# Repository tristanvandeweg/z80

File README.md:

# z80

Our awesome z80 computer!
<br />
# This project is still a work in progress

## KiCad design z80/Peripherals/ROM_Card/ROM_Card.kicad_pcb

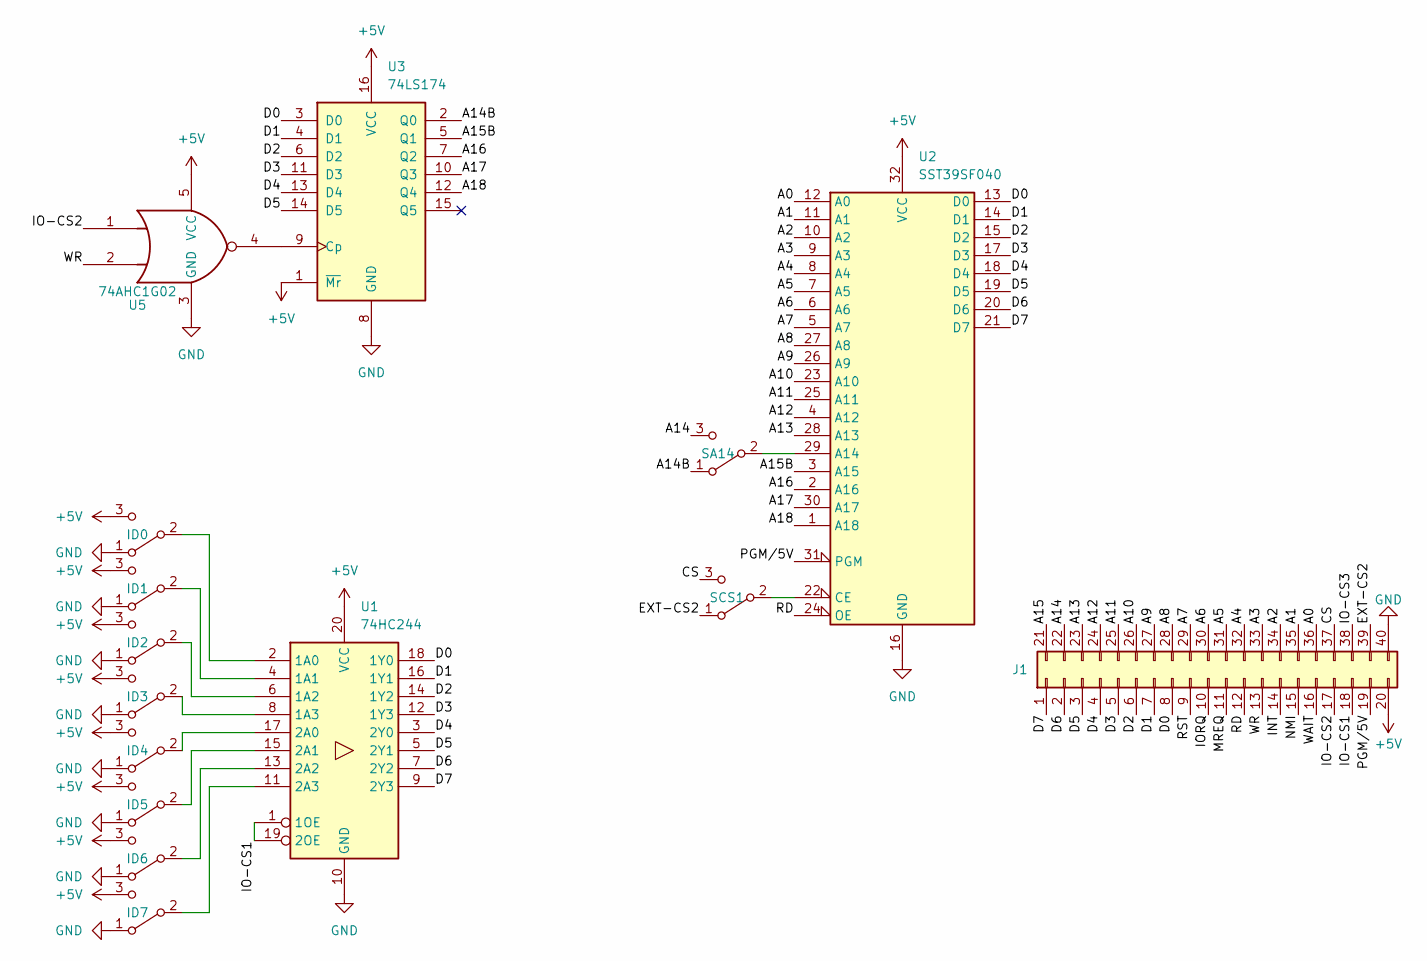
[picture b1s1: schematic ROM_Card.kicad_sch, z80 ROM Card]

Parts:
ID0, ID1, ID2, ID3, ID4, ID5, ID6, ID7: SW_SPDT; SolderJumper-3_P1.3mm_Open_Pad1.0x1.5mm
J1: Conn_02x20_Top_Bottom; 40-pin-edgeconnector
SA14: SW_SPDT; SolderJumper-3_P1.3mm_Open_Pad1.0x1.5mm
SCS1: SW_SPDT; SolderJumper-3_P1.3mm_Open_Pad1.0x1.5mm
U1: 74HC244; TSSOP-20_4.4x6.5mm_P0.65mm
U2: SST39SF040; PLCC-32_THT-Socket
U3: 74LS174; TSSOP-16_4.4x5mm_P0.65mm
U5: 74AHC1G02; SOT-553

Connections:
+5V: ID0.3 (C), ID1.3 (C), ID2.3 (C), ID3.3 (C), ID4.3 (C), ID5.3 (C), ID6.3 (C), ID7.3 (C), J1.20, U1.20 (VCC), U2.32 (VCC), U3.1 (~Mr), U3.16 (VCC), U5.5 (VCC)
/A0: J1.36, U2.12 (A0)
/A1: J1.35, U2.11 (A1)
/A2: J1.34, U2.10 (A2)
/A3: J1.33, U2.9 (A3)
/A4: J1.32, U2.8 (A4)
/A5: J1.31, U2.7 (A5)
/A6: J1.30, U2.6 (A6)
/A7: J1.29, U2.5 (A7)
/A8: J1.28, U2.27 (A8)
/A9: J1.27, U2.26 (A9)
/A10: J1.26, U2.23 (A10)
/A11: J1.25, U2.25 (A11)
/A12: J1.24, U2.4 (A12)
/A13: J1.23, U2.28 (A13)
/A14: J1.22, SA14.3 (C)
/A14B: SA14.1 (A), U3.2 (Q0)
/A15: J1.21
/A15B: U2.3 (A15), U3.5 (Q1)
/A16: U2.2 (A16), U3.7 (Q2)
/A17: U2.30 (A17), U3.10 (Q3)
/A18: U2.1 (A18), U3.12 (Q4)
/CS: J1.37, SCS1.3 (C)
/D0: J1.8, U1.18 (1Y0), U2.13 (D0), U3.3 (D0)
/D1: J1.7, U1.16 (1Y1), U2.14 (D1), U3.4 (D1)
/D2: J1.6, U1.14 (1Y2), U2.15 (D2), U3.6 (D2)
/D3: J1.5, U1.12 (1Y3), U2.17 (D3), U3.11 (D3)
/D4: J1.4, U1.3 (2Y0), U2.18 (D4), U3.13 (D4)
/D5: J1.3, U1.5 (2Y1), U2.19 (D5), U3.14 (D5)
/D6: J1.2, U1.7 (2Y2), U2.20 (D6)
/D7: J1.1, U1.9 (2Y3), U2.21 (D7)
/EXT-CS2: J1.39, SCS1.1 (A)
/INT: J1.14
/IO-CS1: J1.18, U1.1 (1OE), U1.19 (2OE)
/IO-CS2: J1.17, U5.1
/IO-CS3: J1.38
/IORQ: J1.10
/MREQ: J1.11
/NMI: J1.15
/PGM/5V: J1.19, U2.31 (PGM)
/RD: J1.12, U2.24 (OE)
/RST: J1.9
/WAIT: J1.16
/WR: J1.13, U5.2
GND: ID0.1 (A), ID1.1 (A), ID2.1 (A), ID3.1 (A), ID4.1 (A), ID5.1 (A), ID6.1 (A), ID7.1 (A), J1.40, U1.10 (GND), U2.16 (GND), U3.8 (GND), U5.3 (GND)
unnamed: ID0.2 (B), U1.2 (1A0)
unnamed: ID1.2 (B), U1.4 (1A1)
unnamed: ID2.2 (B), U1.6 (1A2)
unnamed: ID3.2 (B), U1.8 (1A3)
unnamed: ID4.2 (B), U1.17 (2A0)
unnamed: ID5.2 (B), U1.15 (2A1)
unnamed: ID6.2 (B), U1.13 (2A2)
unnamed: ID7.2 (B), U1.11 (2A3)
unnamed: SA14.2 (B), U2.29 (A14)
unnamed: SCS1.2 (B), U2.22 (CE)
unnamed: U3.9 (Cp), U5.4

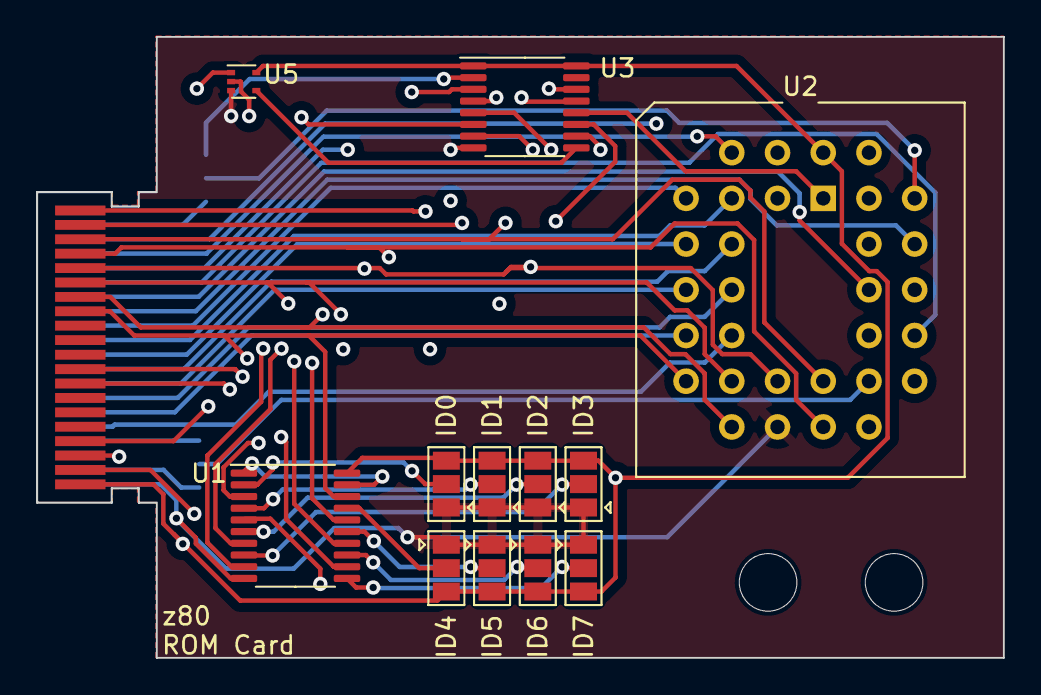
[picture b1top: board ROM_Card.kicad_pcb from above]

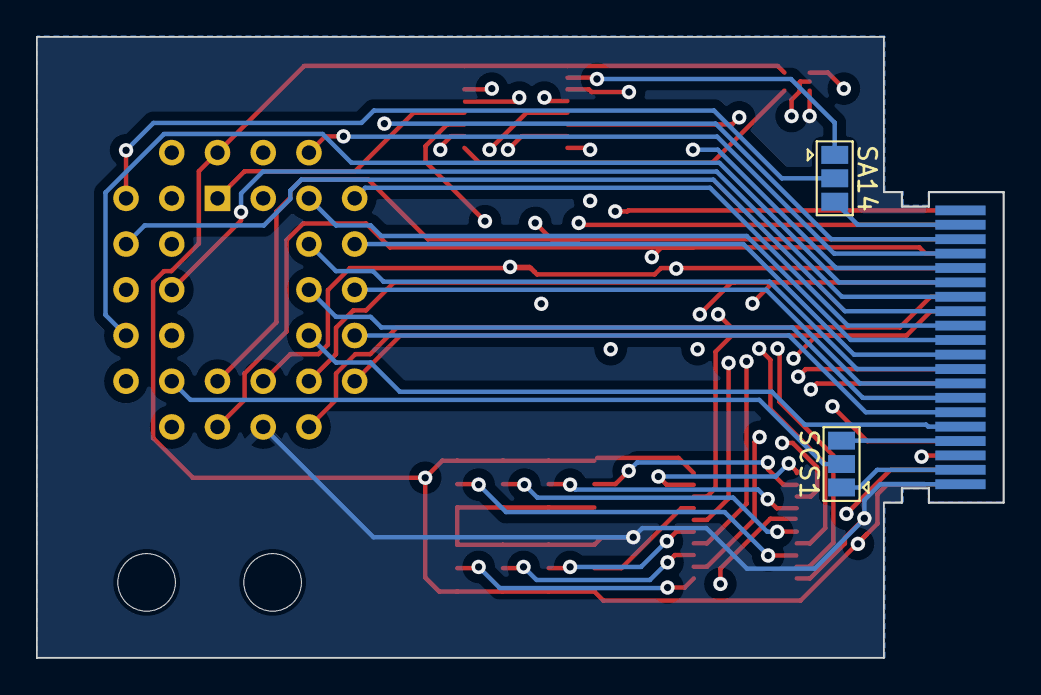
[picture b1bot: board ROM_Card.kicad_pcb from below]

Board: 4 copper layers, 53.7 x 34.5 mm, 15 parts (2 on the bottom side), 48 nets.

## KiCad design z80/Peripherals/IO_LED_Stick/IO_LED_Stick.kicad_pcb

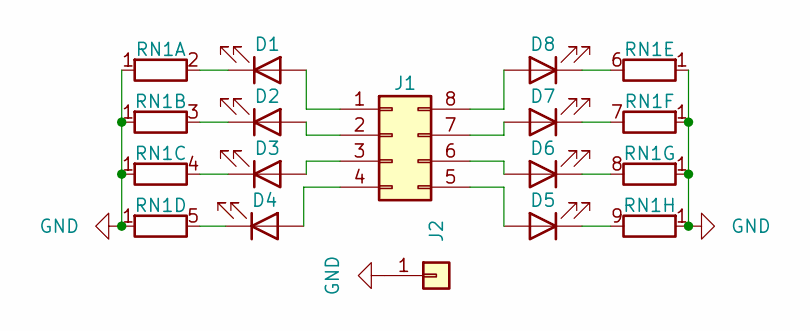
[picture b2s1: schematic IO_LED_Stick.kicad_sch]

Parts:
D1, D2, D3, D4, D5, D6, D7, D8: LED; LED_0603_1608Metric
J1: Conn_02x04_Counter_Clockwise; PinHeader_2x04_P2.54mm_Vertical
J2: Conn_01x01; PinHeader_1x01_P2.54mm_Vertical
RN1: R_Network08_Split; EXB-D10C103J

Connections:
GND: J2.1, RN1.1 (R1)
unnamed: D1.2 (A), J1.1
unnamed: D1.1 (K), RN1.2 (R1.2)
unnamed: D2.2 (A), J1.2
unnamed: D2.1 (K), RN1.3 (R2.2)
unnamed: D3.2 (A), J1.3
unnamed: D3.1 (K), RN1.4 (R3.2)
unnamed: D4.2 (A), J1.4
unnamed: D4.1 (K), RN1.5 (R4.2)
unnamed: D5.2 (A), J1.5
unnamed: D5.1 (K), RN1.9 (R8.2)
unnamed: D6.2 (A), J1.6
unnamed: D6.1 (K), RN1.8 (R7.2)
unnamed: D7.2 (A), J1.7
unnamed: D7.1 (K), RN1.7 (R6.2)
unnamed: D8.2 (A), J1.8
unnamed: D8.1 (K), RN1.6 (R5.2)

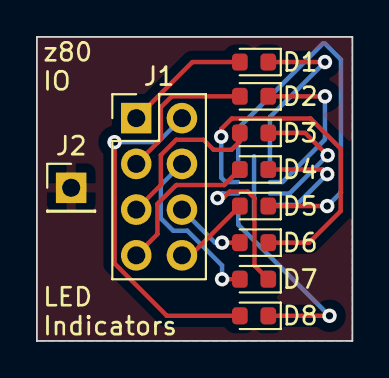
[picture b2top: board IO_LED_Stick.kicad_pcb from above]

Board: 2 copper layers, 17.5 x 16.9 mm, 11 parts (1 on the bottom side), 17 nets.

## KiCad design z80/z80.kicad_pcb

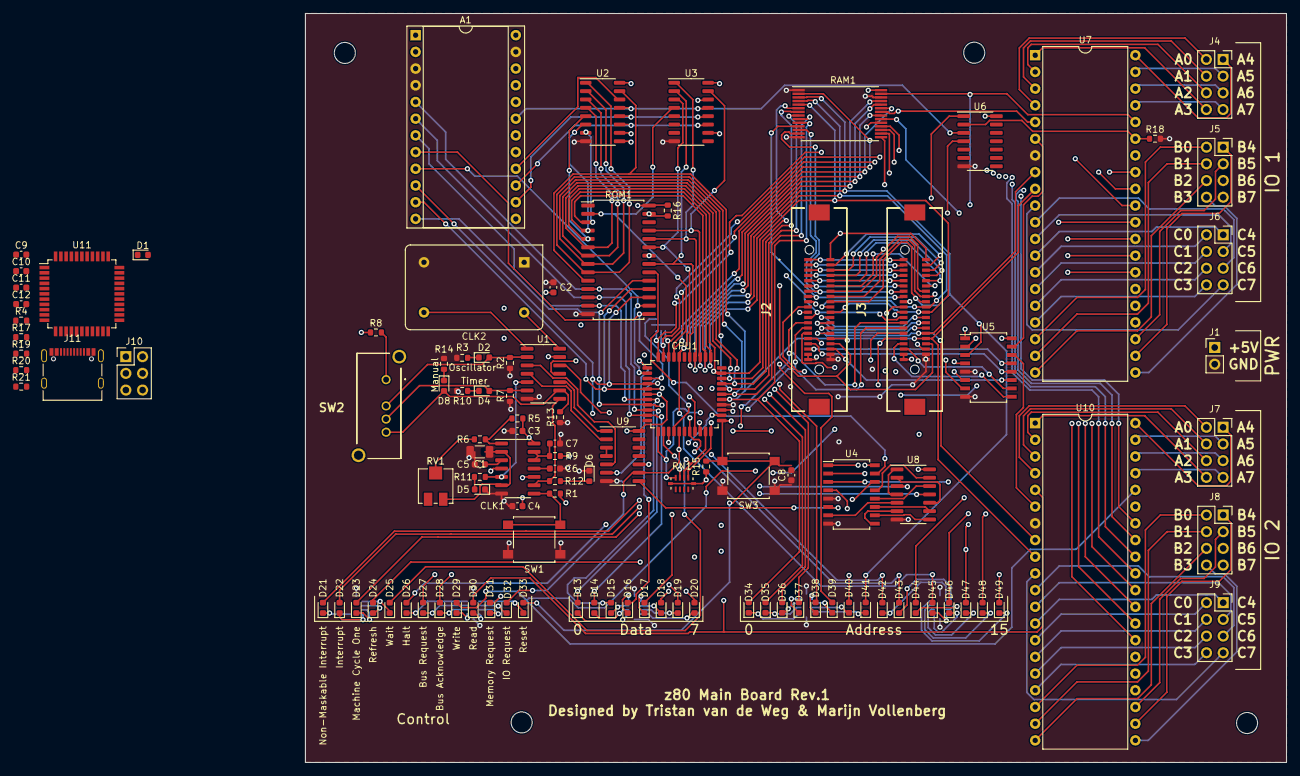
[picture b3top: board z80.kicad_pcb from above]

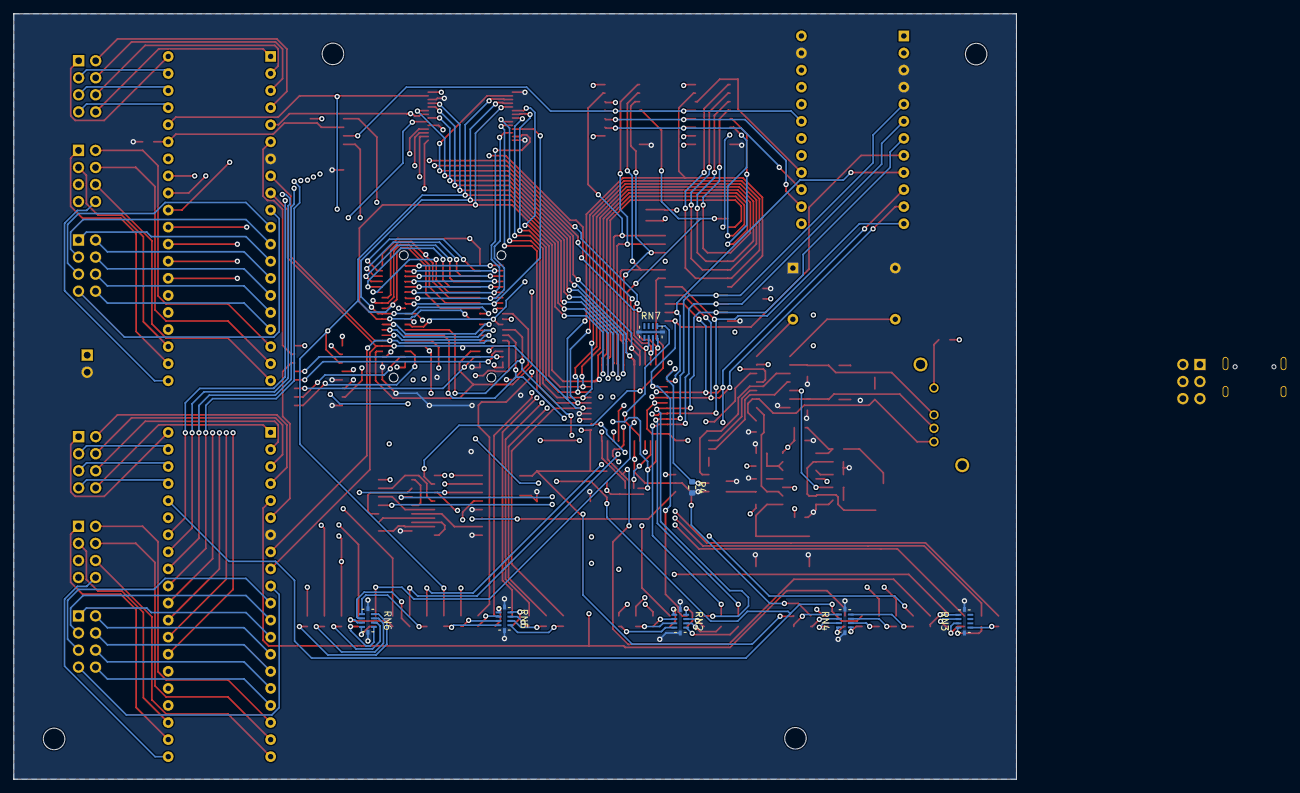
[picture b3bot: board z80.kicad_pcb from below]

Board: 4 copper layers, 149.2 x 113.9 mm, 116 parts (7 on the bottom side), 192 nets.

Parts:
A1: 32U4 Arduino; DIP-24_W15.24mm_Socket
C1: 1uF; C_1206_3216Metric
C2, C3, C4, C5, C6, C7: 0.1uF; C_0603_1608Metric
C8, C11, C12: 1uF; C_0603_1608Metric
C9, C10: 22pF; C_0603_1608Metric
CLK1: NE556; SOIC-14_3.9x8.7mm_P1.27mm
CLK2: TFT680; Oscillator_DIP-14
CPU1: Z84C0010AEG; LQFP-44_10x10mm_P0.8mm
D1: Red; LED_0603_1608Metric
D2, D4, D5, D6, D8: LED_Blue; LED_0603_1608Metric
D13, D14, D15, D16, D17, D18, D19, D20, D34, D35, D36, D37, D38, D39, D40, D41, D42, D43, D44, D45, D46, D47, D48, D49: LED_Yellow; LED_0603_1608Metric
D21, D22, D23, D24, D25, D26, D27, D28, D29, D30, D31, D32, D33: LED_Red; LED_0603_1608Metric
J1: PinHeader_Female01x02; PinHeader_1x02_P2.54mm_Vertical
J2, J3: PinHeader_Female16x02; FX2740S08SV
J4, J5, J6, J7, J8, J9: PinHeader_Female04x02; PinSocket_2x04_P2.54mm_Vertical
J10: Conn_02x03_Counter_Clockwise; PinHeader_2x03_P2.54mm_Vertical
J11: USB_C_Receptacle_USB2.0; USB_C_Receptacle_Palconn_UTC16-G
R1, R3, R5, R6, R8, R10, R14, R15, R21: 1K; R_0603_1608Metric
R2, R4, R4#2, R7, R11, R12, R13, R16, R18, R20: 10K; R_0603_1608Metric
R9: 2M; R_0603_1608Metric
R17, R19: 22R; R_0603_1608Metric
RAM1: HM62256BLP; TSOP-I-28_11.8x8mm_P0.55mm
RN1, RN2, RN3, RN4, RN5, RN6, RN7: EXB-D10C102J; EXB-D10C103J
ROM1: AT28C64B-15SU; SOIC-28W_7.5x17.9mm_P1.27mm
RV1: 1M; Potentiometer_Vishay_TS53YJ_Vertical
SW1, SW3: SW_Push; SW_SPST_B3S-1000
SW2: SW_SP3T; MHS133G04
U1, U8: 4081; SO-14_3.9x8.65mm_P1.27mm
U2, U3: 74HC595; SO-16_3.9x9.9mm_P1.27mm
U4, U5: SN74HC138N; SOIC-16W_5.3x10.2mm_P1.27mm
U6: 4069; SOIC-14_3.9x8.7mm_P1.27mm
U7, U10: 82C55A; DIP-40_W15.24mm
U9: 74LS32; SOIC-14_3.9x8.7mm_P1.27mm
U11: ATmega32U4RC-A; TQFP-44_10x10mm_P0.8mm

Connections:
+5V: A1.4 (+5V), C2.2, C3.2, C4.2, CLK1.4 (R), CLK1.10 (R), CLK1.14 (VCC), CLK2.14 (Vcc), CPU1.6 (VCC), D1.2 (A), J1.1, J2.19, J2.20, J3.19, J3.20, J10.2, R1.1, R4.1, R5.1, R8.1, R9.1, R15.2, R16.1, R20.2, RAM1.28 (VCC), RN1.1 (common), ROM1.28 (VCC), U1.14 (VDD), U2.10 (~SRCLR), U2.16 (VCC), U3.10 (~SRCLR), U3.16 (VCC), U4.16 (VCC), U5.16 (VCC), U6.14 (VDD), U7.26 (VCC), U8.14 (VDD), U9.14 (VCC), U10.26 (VCC), U11.14 (VCC), U11.24 (AVCC), U11.34 (VCC), U11.44 (AVCC)
/A0: CPU1.27 (A0), D34.2 (A), J2.36, J3.36, RAM1.10 (A0), ROM1.10 (A0), U2.15 (QA), U7.9 (A0), U10.9 (A0)
/A1: CPU1.28 (A1), D35.2 (A), J2.35, J3.35, RAM1.9 (A1), ROM1.9 (A1), U2.1 (QB), U7.8 (A1), U10.8 (A1)
/A2: CPU1.29 (A2), D36.2 (A), J2.34, J3.34, RAM1.8 (A2), ROM1.8 (A2), U2.2 (QC)
/A3: CPU1.30 (A3), D37.2 (A), J2.33, J3.33, RAM1.7 (A3), ROM1.7 (A3), U2.3 (QD)
/A4: CPU1.31 (A4), D38.2 (A), J2.32, J3.32, RAM1.6 (A4), ROM1.6 (A4), U2.4 (QE)
/A5: CPU1.32 (A5), D39.2 (A), J2.31, J3.31, RAM1.5 (A5), ROM1.5 (A5), U2.5 (QF), U5.1 (A)
/A6: CPU1.34 (A6), D40.2 (A), J2.30, J3.30, RAM1.4 (A6), ROM1.4 (A6), U2.6 (QG), U5.2 (B)
/A7: CPU1.35 (A7), D41.2 (A), J2.29, J3.29, RAM1.3 (A7), ROM1.3 (A7), U2.7 (QH), U5.3 (C)
/A8: CPU1.36 (A8), D42.2 (A), J2.28, J3.28, RAM1.25 (A8), ROM1.25 (A8), U3.15 (QA)
/A9: CPU1.37 (A9), D43.2 (A), J2.27, J3.27, RAM1.24 (A9), ROM1.24 (A9), U3.1 (QB)
/A10: CPU1.38 (A10), D44.2 (A), J2.26, J3.26, RAM1.21 (A10), ROM1.21 (A10), U3.2 (QC)
/A11: CPU1.40 (A11), D45.2 (A), J2.25, J3.25, RAM1.23 (A11), ROM1.23 (A11), U3.3 (QD)
/A12: CPU1.41 (A12), D46.2 (A), J2.24, J3.24, RAM1.2 (A12), ROM1.2 (A12), U3.4 (QE)
/A13: CPU1.42 (A13), D47.2 (A), J2.23, J3.23, RN7.7 (R6), U4.1 (A)
/A14: CPU1.43 (A14), D48.2 (A), J2.22, J3.22, RN7.8 (R7), U4.2 (B)
/A15: CPU1.44 (A15), D49.2 (A), J2.21, J3.21, RN7.9 (R8), U4.3 (C)
/AdjClk: CLK1.5 (Q), R11.2, U1.5
/AdjOUT: U1.4, U9.2
/BUSACK: A1.5 (A3), CPU1.20 (~BUSACK), D28.2 (A)
/BUSRQ: A1.12 (D10), CPU1.22 (~BUSRQ), D27.2 (A), RN1.2 (R1)
/D0: A1.20 (D2), CPU1.9 (D0), D13.2 (A), J2.8, J3.8, RAM1.11 (Q0), ROM1.11 (I/O0), U7.34 (D0), U10.34 (D0)
/D1: A1.19 (D3), CPU1.10 (D1), D14.2 (A), J2.7, J3.7, RAM1.12 (Q1), ROM1.12 (I/O1), U7.33 (D1), U10.33 (D1)
/D2: A1.18 (D4), CPU1.7 (D2), D15.2 (A), J2.6, J3.6, RAM1.13 (Q2), ROM1.13 (I/O2), U7.32 (D2), U10.32 (D2)
/D3: A1.17 (D5), CPU1.3 (D3), D16.2 (A), J2.5, J3.5, RAM1.15 (Q3), ROM1.15 (I/O3), U7.31 (D3), U10.31 (D3)
/D4: A1.16 (D6), CPU1.2 (D4), D17.2 (A), J2.4, J3.4, RAM1.16 (Q4), ROM1.16 (I/O4), U7.30 (D4), U10.30 (D4)
/D5: A1.15 (D7), CPU1.4 (D5), D18.2 (A), J2.3, J3.3, RAM1.17 (Q5), ROM1.17 (I/O5), U7.29 (D5), U10.29 (D5)
/D6: A1.14 (D8), CPU1.5 (D6), D19.2 (A), J2.2, J3.2, RAM1.18 (Q6), ROM1.18 (I/O6), U7.28 (D6), U10.28 (D6)
/D7: A1.13 (D9), CPU1.8 (D7), D20.2 (A), J2.1, J3.1, RAM1.19 (Q7), ROM1.19 (I/O7), U7.27 (D7), U10.27 (D7)
/EXT-CS: J2.37, J3.37, U1.11
/EXT-IO1-CS: J2.18, U5.13 (Y2)
/EXT-IO2-CS: J2.17, U5.12 (Y3)
/EXT-IO3-CS: J2.38, U5.11 (Y4)
/EXT-IO4-CS: J3.18, U5.10 (Y5)
/EXT-IO5-CS: J3.17, U5.9 (Y6)
/EXT-IO6-CS: J3.38, U5.7 (Y7)
/FstClk: CLK2.8 (OUT), U1.1
/FstOUT: U1.3, U9.5
/HALT: CPU1.14 (~HALT), D26.2 (A)
/INT: CPU1.12 (~INT), D22.2 (A), J2.14, J3.14, RN1.5 (R4)
/IO1-CS: U5.15 (Y0), U7.6 (~CS)
/IO2-CS: U5.14 (Y1), U10.6 (~CS)
/IOREQ: U4.6 (G1), U5.4 (~G2A), U9.8
/IORQ: CPU1.16 (~IORQ), D32.2 (A), J2.10, J3.10, U9.9
/M1: CPU1.24 (~M1), D23.2 (A)
/MISO: J10.1, U11.11 (PB3)
/MOSI: J10.4, U11.10 (PB2)
/MREQ: CPU1.15 (~MREQ), D31.2 (A), J2.11, J3.11, RN7.2 (R1), U4.4 (~G2A), U5.6 (G1)
/ManClk: CLK1.9 (Q), R12.1, U1.8
/ManOUT: U1.10, U9.1
/NMI: CPU1.13 (~NMI), D21.2 (A), J2.15, J3.15, RN1.4 (R3)
/PROG-OE: A1.6 (A2), R20.1, U2.13 (~OE), U3.13 (~OE), U6.3
/PROG-WR: A1.7 (A1), R16.2, ROM1.27 (~WE)
/ProgReset: J10.5, R4.2, U11.13 (~RESET)
/RAM1-CS: RAM1.20 (~CS), U4.14 (Y1)
/RD: A1.8 (A0), CPU1.18 (~RD), D30.2 (A), J2.12, J3.12, RAM1.22 (~OE), ROM1.22 (~OE), U7.5 (~RD), U10.5 (~RD)
/RFSH: CPU1.25 (~RFSH), D24.2 (A)
/ROM1-CS: ROM1.20 (~CE), U4.15 (Y0)
/RST: C8.2, CPU1.23 (~RESET), D33.2 (A), J2.9, J3.9, R15.1, SW3.2, U6.1
/RST-INV: R18.1, U6.2, U7.35 (RESET), U10.35 (RESET)
/SPISCK: J10.3, U11.9 (PB1)
/USB-D+: J11.A6 (D+), J11.B6 (D+), R17.1
/USB-D-: J11.A7 (D-), J11.B7 (D-), R19.1
/VBUS: C12.2, J11.A4 (VBUS), J11.A9 (VBUS), J11.B4 (VBUS), J11.B9 (VBUS), U11.2 (UVCC), U11.7 (VBUS)
/WAIT: CPU1.21 (~WAIT), D25.2 (A), J2.16, J3.16, RN1.3 (R2)
/WR: CPU1.19 (~WR), D29.2 (A), J2.13, J3.13, RAM1.27 (~WE), U7.36 (~WR), U10.36 (~WR)
Clock: CPU1.1 (~CLK), R4#2.1, U9.6
GND: A1.2 (GND), A1.21 (GND), A1.22 (GND), C1.2, C2.1, C3.1, C4.1, C5.2, C6.2, C7.1, C8.1, C9.2, C10.2, C11.2, C12.1, CLK1.7 (GND), CLK2.1 (EN), CLK2.7 (GND), CPU1.26 (GND), D5.1 (K), D6.1 (K), J1.2, J2.39, J2.40, J3.39, J3.40, J10.6, J11.A1 (GND), J11.A12 (GND), J11.B1 (GND), J11.B12 (GND), J11.S1 (SHIELD), R2.1, R3.2, R4#2.2, R7.1, R10.2, R13.1, R14.2, R18.2, RAM1.1 (A14), RAM1.14 (GND), RAM1.26 (A13), RN2.1 (common), RN3.1 (common), RN4.1 (common), RN5.1 (common), RN6.1 (common), RN7.1 (common), ROM1.14 (GND), SW1.1, SW3.1, U1.7 (VSS), U2.8 (GND), U3.8 (GND), U4.5 (~G2B), U4.8 (GND), U5.5 (~G2B), U5.8 (GND), U6.7 (VSS), U7.7 (GND), U8.7 (VSS), U9.7 (GND), U10.7 (GND), U11.5 (UGND), U11.15 (GND), U11.23 (GND), U11.33 (~HWB/PE2), U11.35 (GND), U11.43 (GND)
unnamed: A1.10 (D14), U2.11 (SRCLK), U3.11 (SRCLK)
unnamed: A1.9 (D15), U2.14 (SER)
unnamed: A1.11 (D16), U2.12 (RCLK), U3.12 (RCLK)
unnamed: C5.1, CLK1.3 (CV)
unnamed: CLK1.1 (DIS), R5.2, R6.2
unnamed: C1.1, CLK1.2 (THR), CLK1.6 (TR), RV1.1
unnamed: C6.1, CLK1.11 (CV)
unnamed: C7.2, CLK1.12 (THR), CLK1.13 (DIS), R9.2
unnamed: CLK1.8 (TR), R1.2, SW1.2
unnamed: D1.1 (K), R21.1
unnamed: D2.2 (A), R2.2, SW2.1, U1.2
unnamed: D2.1 (K), R3.1
unnamed: D4.2 (A), R7.2, SW2.3, U1.6
unnamed: D4.1 (K), R10.1
unnamed: D5.2 (A), R11.1
unnamed: D6.2 (A), R12.2
unnamed: D8.2 (A), R13.2, SW2.4, U1.9
unnamed: D8.1 (K), R14.1
unnamed: D13.1 (K), RN2.2 (R1)
unnamed: D14.1 (K), RN2.3 (R2)
unnamed: D15.1 (K), RN2.4 (R3)
unnamed: D16.1 (K), RN2.5 (R4)
unnamed: D17.1 (K), RN2.6 (R5)
unnamed: D18.1 (K), RN2.7 (R6)
unnamed: D19.1 (K), RN2.8 (R7)
unnamed: D20.1 (K), RN2.9 (R8)
unnamed: D21.1 (K), RN3.6 (R5)
unnamed: D22.1 (K), RN3.5 (R4)
unnamed: D23.1 (K), RN3.4 (R3)
unnamed: D24.1 (K), RN3.3 (R2)
unnamed: D25.1 (K), RN3.2 (R1)
unnamed: D26.1 (K), RN4.9 (R8)
unnamed: D27.1 (K), RN4.8 (R7)
unnamed: D28.1 (K), RN4.7 (R6)
unnamed: D29.1 (K), RN4.6 (R5)
unnamed: D30.1 (K), RN4.5 (R4)
unnamed: D31.1 (K), RN4.4 (R3)
unnamed: D32.1 (K), RN4.3 (R2)
unnamed: D33.1 (K), RN4.2 (R1)
unnamed: D34.1 (K), RN5.2 (R1)
unnamed: D35.1 (K), RN5.3 (R2)
unnamed: D36.1 (K), RN5.4 (R3)
unnamed: D37.1 (K), RN5.5 (R4)
unnamed: D38.1 (K), RN5.6 (R5)
unnamed: D39.1 (K), RN5.7 (R6)
unnamed: D40.1 (K), RN5.8 (R7)
unnamed: D41.1 (K), RN5.9 (R8)
unnamed: D42.1 (K), RN6.2 (R1)
unnamed: D43.1 (K), RN6.3 (R2)
unnamed: D44.1 (K), RN6.4 (R3)
unnamed: D45.1 (K), RN6.5 (R4)
unnamed: D46.1 (K), RN6.6 (R5)
unnamed: D47.1 (K), RN6.7 (R6)
unnamed: D48.1 (K), RN6.8 (R7)
unnamed: D49.1 (K), RN6.9 (R8)
unnamed: J4.1, U7.40 (PA4)
unnamed: J4.2, U7.4 (PA0)
unnamed: J4.3, U7.39 (PA5)
unnamed: J4.4, U7.3 (PA1)
unnamed: J4.5, U7.38 (PA6)
unnamed: J4.6, U7.2 (PA2)
unnamed: J4.7, U7.37 (PA7)
unnamed: J4.8, U7.1 (PA3)
unnamed: J5.1, U7.22 (PB4)
unnamed: J5.2, U7.18 (PB0)
unnamed: J5.3, U7.23 (PB5)
unnamed: J5.4, U7.19 (PB1)
unnamed: J5.5, U7.24 (PB6)
unnamed: J5.6, U7.20 (PB2)
unnamed: J5.7, U7.25 (PB7)
unnamed: J5.8, U7.21 (PB3)
unnamed: J6.1, U7.13 (PC4)
unnamed: J6.2, U7.14 (PC0)
unnamed: J6.3, U7.12 (PC5)
unnamed: J6.4, U7.15 (PC1)
unnamed: J6.5, U7.11 (PC6)
unnamed: J6.6, U7.16 (PC2)
unnamed: J6.7, U7.10 (PC7)
unnamed: J6.8, U7.17 (PC3)
unnamed: J7.1, U10.40 (PA4)
unnamed: J7.2, U10.4 (PA0)
unnamed: J7.3, U10.39 (PA5)
unnamed: J7.4, U10.3 (PA1)
unnamed: J7.5, U10.38 (PA6)
unnamed: J7.6, U10.2 (PA2)
unnamed: J7.7, U10.37 (PA7)
unnamed: J7.8, U10.1 (PA3)
unnamed: J8.1, U10.22 (PB4)
unnamed: J8.2, U10.18 (PB0)
unnamed: J8.3, U10.23 (PB5)
unnamed: J8.4, U10.19 (PB1)
unnamed: J8.5, U10.24 (PB6)
unnamed: J8.6, U10.20 (PB2)
unnamed: J8.7, U10.25 (PB7)
unnamed: J8.8, U10.21 (PB3)
unnamed: J9.1, U10.13 (PC4)
unnamed: J9.2, U10.14 (PC0)
unnamed: J9.3, U10.12 (PC5)
unnamed: J9.4, U10.15 (PC1)
unnamed: J9.5, U10.11 (PC6)
unnamed: J9.6, U10.16 (PC2)
unnamed: J9.7, U10.10 (PC7)
unnamed: J9.8, U10.17 (PC3)
unnamed: R6.1, RV1.2
unnamed: R8.2, SW2.2
unnamed: U1.12, U8.3
unnamed: U1.13, U8.11
unnamed: U2.9 (QH'), U3.14 (SER)
unnamed: U4.13 (Y2), U8.13
unnamed: U4.12 (Y3), U8.12
unnamed: U4.11 (Y4), U8.9
unnamed: U4.10 (Y5), U8.8
unnamed: U4.9 (Y6), U8.6
unnamed: U4.7 (Y7), U8.5
unnamed: U6.4, U9.10
unnamed: U8.1, U8.4
unnamed: U8.2, U8.10
unnamed: U9.3, U9.4
unnamed: R17.2, U11.4 (D+)
unnamed: R19.2, U11.3 (D-)
unnamed: R21.2, U11.8 (PB0)
unnamed: C11.1, U11.6 (UCAP)
unnamed: C9.1, U11.17 (XTAL1)
unnamed: C10.1, U11.16 (XTAL2)

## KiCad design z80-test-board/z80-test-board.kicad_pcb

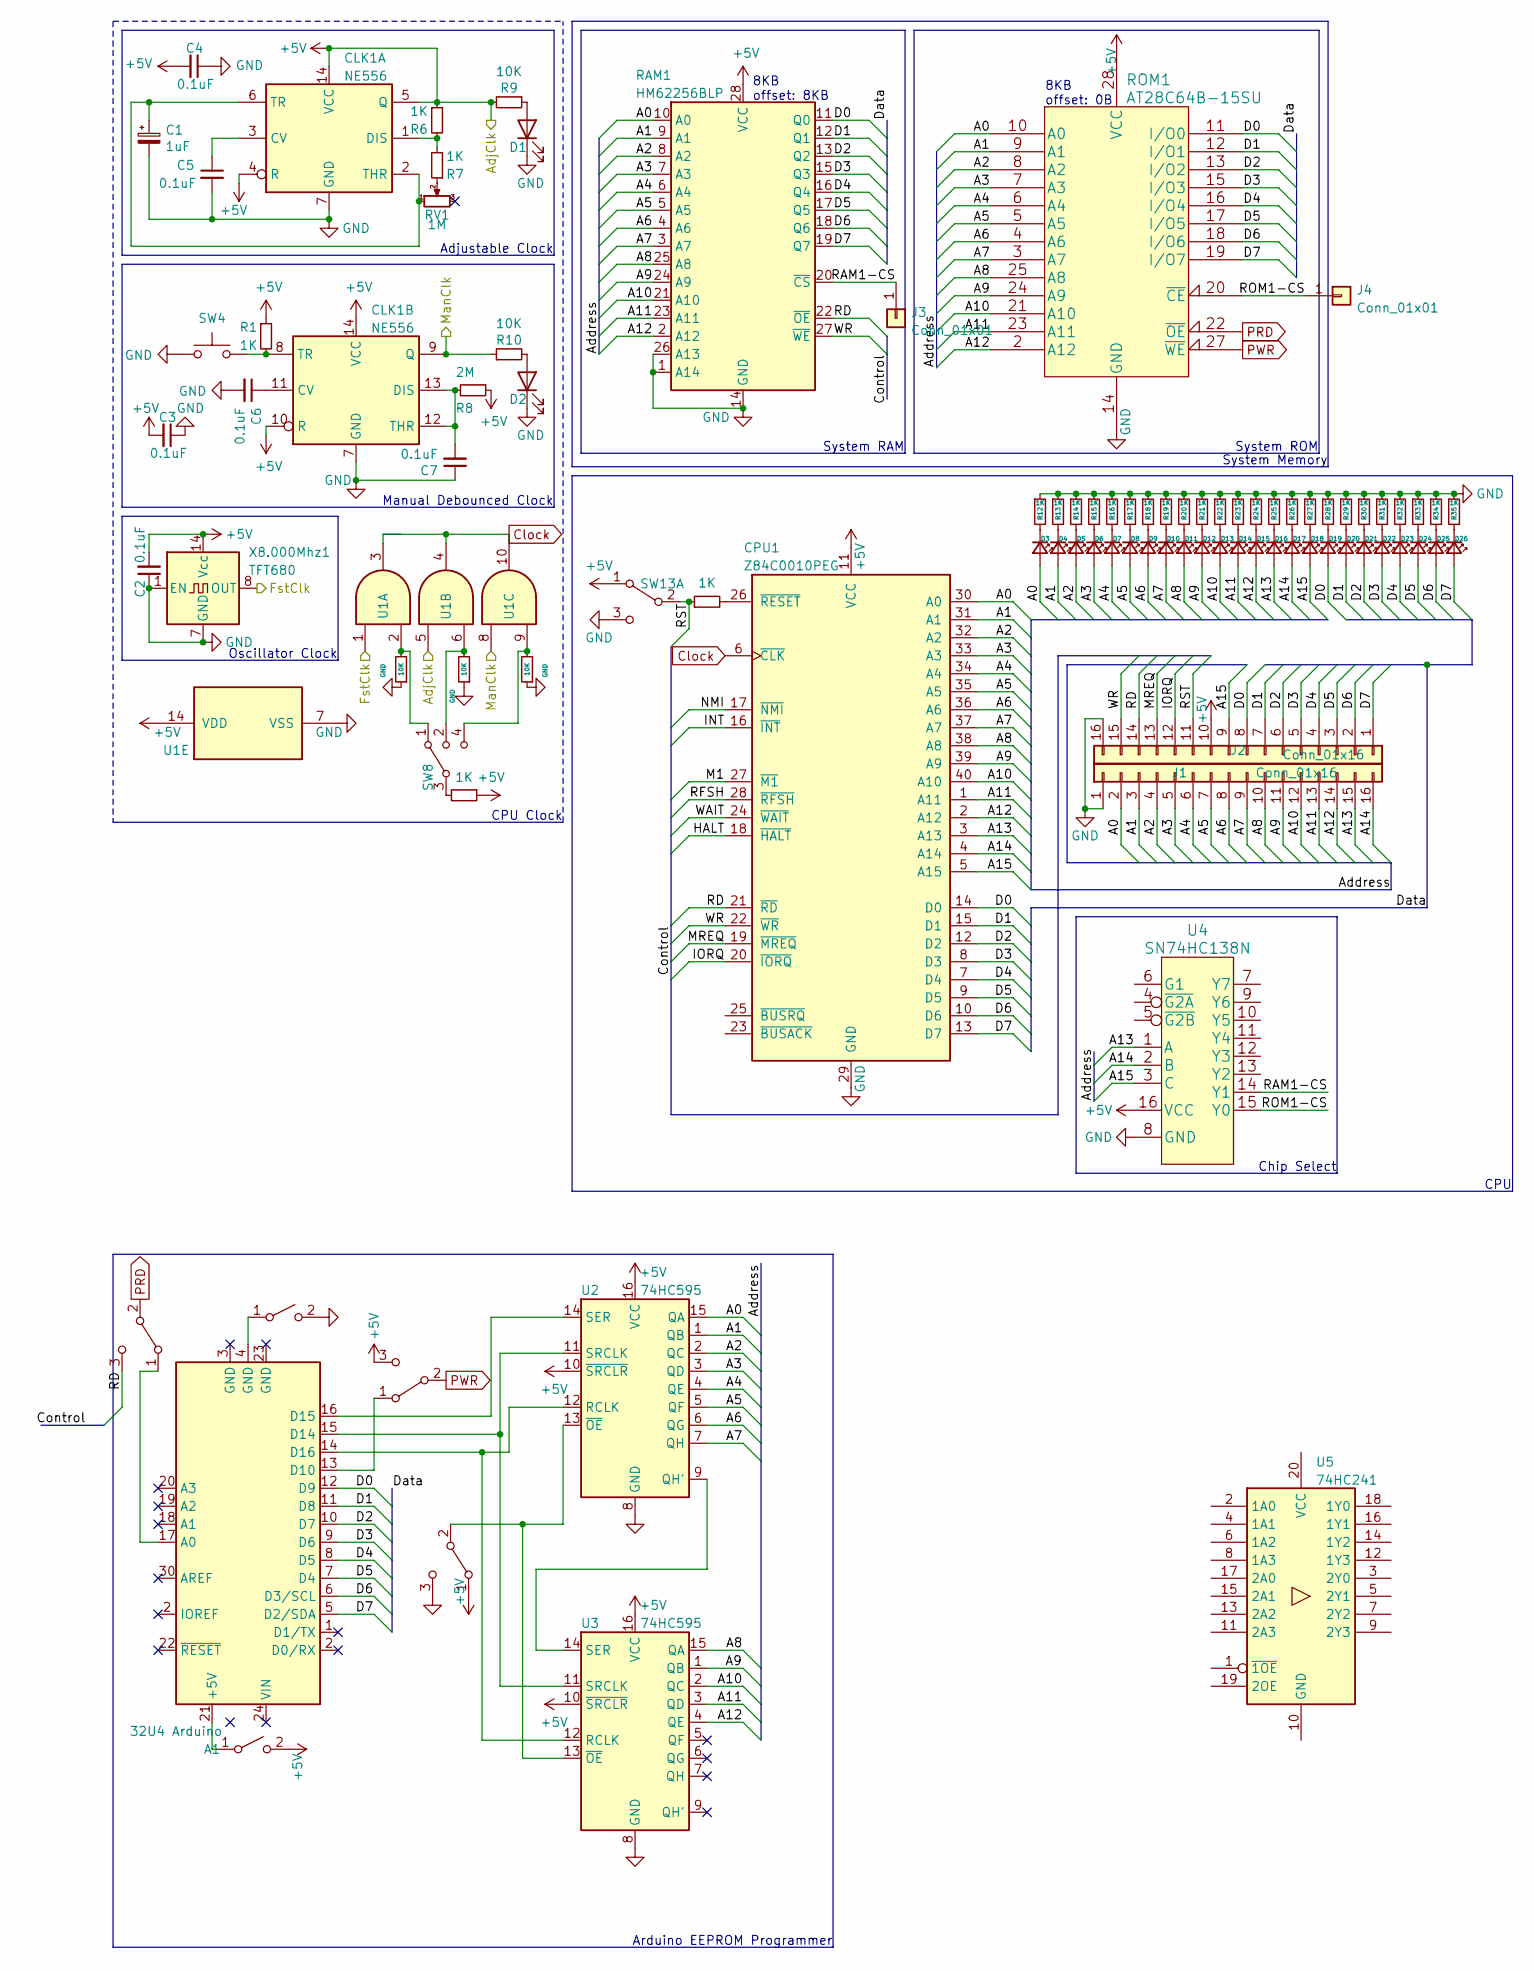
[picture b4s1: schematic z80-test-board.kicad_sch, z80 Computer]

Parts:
A1: 32U4 Arduino; DIP-24_W15.24mm_Socket
C1: 1uF; C_0805_2012Metric_Pad1.18x1.45mm_HandSolder
C2, C3, C4, C5, C6, C7: 0.1uF; C_0805_2012Metric_Pad1.18x1.45mm_HandSolder
CLK1: NE556; DIP-14_W7.62mm_Socket
CPU1: Z84C0010PEG; DIP-40_W15.24mm_Socket
D1, D2: LED; LED_0603_1608Metric_Pad1.05x0.95mm_HandSolder
D3, D4, D5, D6, D7, D8, D9, D10, D11, D12, D13, D14, D15, D16, D17, D18, D19, D20, D21, D22, D23, D24, D25, D26: LED_Small; LED_0603_1608Metric_Pad1.05x0.95mm_HandSolder
J1, J2: Conn_01x16; PinHeader_1x16_P2.54mm_Vertical
J3, J4: Conn_01x01; PinHeader_1x01_P2.54mm_Vertical
R1, R2, R7, R11, R12, R13, R14, R15, R16, R17, R18, R19, R20, R21, R22, R23, R24, R25, R26, R27, R28, R29, R30, R31, R32, R33, R34, R35: 1K; R_0603_1608Metric_Pad0.98x0.95mm_HandSolder
R3, R4, R5, R9, R10: 10K; R_0603_1608Metric_Pad0.98x0.95mm_HandSolder
R6: 1K; R_0603_1608Metric
R8: 2M; R_0603_1608Metric_Pad0.98x0.95mm_HandSolder
RAM1: HM62256BLP; DIP-28_W15.24mm_Socket
ROM1: AT28C64B-15SU; DIP-28_W15.24mm_Socket
RV1: 1M; Potentiometer_ACP_CA9-V10_Vertical
SW1, SW7: SW_SPST; PinHeader_1x03_P2.54mm_Vertical
SW2, SW3, SW11: SW_SPDT; PinHeader_1x03_P2.54mm_Vertical
SW4: SW_Push; SW_PUSH_6mm
SW8: SW_SP3T; SW_SP3T_PCM13
SW13: SW_DPDT_x2; PinHeader_1x03_P2.54mm_Vertical
U1: 4081; SO-14_3.9x8.65mm_P1.27mm
U2, U3: 74HC595; SO-16_3.9x9.9mm_P1.27mm
U4: SN74HC138N
U5: 74HC241
X8.000Mhz1: TFT680; Oscillator_DIP-14

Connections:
+5V: C2.2, C3.2, C4.2, CLK1.4 (R), CLK1.5 (Q), CLK1.10 (R), CLK1.14 (VCC), CPU1.11 (VCC), J2.10, R1.1, R2.1, R6.1, R8.1, R9.2, RAM1.28 (VCC), ROM1.28 (VCC), SW1.2 (B), SW2.1 (A), SW11.3 (C), SW13.1 (A), U1.5, U1.14 (VDD), U2.10 (~SRCLR), U2.16 (VCC), U3.10 (~SRCLR), U3.16 (VCC), U4.16 (VCC), X8.000Mhz1.14 (Vcc)
/A0: CPU1.30 (A0), D3.2 (A), J1.2, RAM1.10 (A0), ROM1.10 (A0), U2.15 (QA)
/A1: CPU1.31 (A1), D4.2 (A), J1.3, RAM1.9 (A1), ROM1.9 (A1), U2.1 (QB)
/A2: CPU1.32 (A2), D5.2 (A), J1.4, RAM1.8 (A2), ROM1.8 (A2), U2.2 (QC)
/A3: CPU1.33 (A3), D6.2 (A), J1.5, RAM1.7 (A3), ROM1.7 (A3), U2.3 (QD)
/A4: CPU1.34 (A4), D7.2 (A), J1.6, RAM1.6 (A4), ROM1.6 (A4), U2.4 (QE)
/A5: CPU1.35 (A5), D8.2 (A), J1.7, RAM1.5 (A5), ROM1.5 (A5), U2.5 (QF)
/A6: CPU1.36 (A6), D9.2 (A), J1.8, RAM1.4 (A6), ROM1.4 (A6), U2.6 (QG)
/A7: CPU1.37 (A7), D10.2 (A), J1.9, RAM1.3 (A7), ROM1.3 (A7), U2.7 (QH)
/A8: CPU1.38 (A8), D11.2 (A), J1.10, RAM1.25 (A8), ROM1.25 (A8), U3.15 (QA)
/A9: CPU1.39 (A9), D12.2 (A), J1.11, RAM1.24 (A9), ROM1.24 (A9), U3.1 (QB)
/A10: CPU1.40 (A10), D13.2 (A), J1.12, RAM1.21 (A10), ROM1.21 (A10), U3.2 (QC)
/A11: CPU1.1 (A11), D14.2 (A), J1.13, RAM1.23 (A11), ROM1.23 (A11), U3.3 (QD)
/A12: CPU1.2 (A12), D15.2 (A), J1.14, RAM1.2 (A12), ROM1.2 (A12), U3.4 (QE)
/A13: CPU1.3 (A13), D16.2 (A), J1.15, U4.1 (A)
/A14: CPU1.4 (A14), D17.2 (A), J1.16, U4.2 (B)
/A15: CPU1.5 (A15), D18.2 (A), J2.9, U4.3 (C)
/D0: A1.12 (D9), CPU1.14 (D0), D19.2 (A), J2.8, RAM1.11 (Q0), ROM1.11 (I/O0)
/D1: A1.11 (D8), CPU1.15 (D1), D20.2 (A), J2.7, RAM1.12 (Q1), ROM1.12 (I/O1)
/D2: A1.10 (D7), CPU1.12 (D2), D21.2 (A), J2.6, RAM1.13 (Q2), ROM1.13 (I/O2)
/D3: A1.9 (D6), CPU1.8 (D3), D22.2 (A), J2.5, RAM1.15 (Q3), ROM1.15 (I/O3)
/D4: A1.8 (D5), CPU1.7 (D4), D23.2 (A), J2.4, RAM1.16 (Q4), ROM1.16 (I/O4)
/D5: A1.7 (D4), CPU1.9 (D5), D24.2 (A), J2.3, RAM1.17 (Q5), ROM1.17 (I/O5)
/D6: A1.6 (D3/SCL), CPU1.10 (D6), D25.2 (A), J2.2, RAM1.18 (Q6), ROM1.18 (I/O6)
/D7: A1.5 (D2/SDA), CPU1.13 (D7), D26.2 (A), J2.1, RAM1.19 (Q7), ROM1.19 (I/O7)
/FstClk: U1.1, X8.000Mhz1.8 (OUT)
/HALT: CPU1.18 (~HALT)
/INT: CPU1.16 (~INT)
/IORQ: CPU1.20 (~IORQ), J2.12
/M1: CPU1.27 (~M1)
/MREQ: CPU1.19 (~MREQ), J2.13
/ManClk: CLK1.9 (Q), R10.1, U1.8
/NMI: CPU1.17 (~NMI)
/RAM1-CS: J3.1, RAM1.20 (~CS), U4.14 (Y1)
/RD: CPU1.21 (~RD), J2.14, RAM1.22 (~OE), SW3.3 (C)
/RFSH: CPU1.28 (~RFSH)
/ROM1-CS: J4.1, ROM1.20 (~CE), U4.15 (Y0)
/RST: J2.11, R11.1, SW13.2 (B)
/WAIT: CPU1.24 (~WAIT)
/WR: CPU1.22 (~WR), J2.15, RAM1.27 (~WE)
Clock: CPU1.6 (~CLK), U1.3, U1.4, U1.10
GND: C1.2, C2.1, C3.1, C4.1, C5.2, C6.2, C7.1, CLK1.7 (GND), CPU1.29 (GND), D1.1 (K), D2.1 (K), J1.1, J2.16, R3.1, R4.1, R5.1, R12.1, R13.1, R14.1, R15.1, R16.1, R17.1, R18.1, R19.1, R20.1, R21.1, R22.1, R23.1, R24.1, R25.1, R26.1, R27.1, R28.1, R29.1, R30.1, R31.1, R32.1, R33.1, R34.1, R35.1, RAM1.1 (A14), RAM1.14 (GND), RAM1.26 (A13), ROM1.14 (GND), SW2.3 (C), SW4.1, SW7.2 (B), SW13.3 (C), U1.7 (VSS), U2.8 (GND), U3.8 (GND), U4.8 (GND), X8.000Mhz1.1 (EN), X8.000Mhz1.7 (GND)
unnamed: A1.4 (GND), SW7.1 (A)
unnamed: A1.13 (D10), SW11.1 (A)
unnamed: A1.14 (D16), U2.12 (RCLK), U3.12 (RCLK)
unnamed: A1.15 (D14), U2.11 (SRCLK), U3.11 (SRCLK)
unnamed: A1.16 (D15), U2.14 (SER)
unnamed: A1.17 (A0), SW3.1 (A)
unnamed: A1.21 (+5V), SW1.1 (A)
unnamed: C1.1, CLK1.2 (THR), CLK1.6 (TR), RV1.1
unnamed: C5.1, CLK1.3 (CV)
unnamed: C6.1, CLK1.11 (CV)
unnamed: C7.2, CLK1.12 (THR), CLK1.13 (DIS), R8.2
unnamed: CLK1.1 (DIS), R6.2, R7.2
unnamed: CLK1.8 (TR), R1.2, SW4.2
unnamed: CPU1.26 (~RESET), R11.2
unnamed: D1.2 (A), R9.1
unnamed: D2.2 (A), R10.2
unnamed: D3.1 (K), R12.2
unnamed: D4.1 (K), R13.2
unnamed: D5.1 (K), R14.2
unnamed: D6.1 (K), R15.2
unnamed: D7.1 (K), R16.2
unnamed: D8.1 (K), R17.2
unnamed: D9.1 (K), R18.2
unnamed: D10.1 (K), R19.2
unnamed: D11.1 (K), R20.2
unnamed: D12.1 (K), R21.2
unnamed: D13.1 (K), R22.2
unnamed: D14.1 (K), R23.2
unnamed: D15.1 (K), R24.2
unnamed: D16.1 (K), R25.2
unnamed: D17.1 (K), R26.2
unnamed: D18.1 (K), R27.2
unnamed: D19.1 (K), R28.2
unnamed: D20.1 (K), R29.2
unnamed: D21.1 (K), R30.2
unnamed: D22.1 (K), R31.2
unnamed: D23.1 (K), R32.2
unnamed: D24.1 (K), R33.2
unnamed: D25.1 (K), R34.2
unnamed: D26.1 (K), R35.2
unnamed: R2.2, SW8.3
unnamed: R3.2, SW8.1, U1.2
unnamed: R4.2, SW8.2, U1.6
unnamed: R5.2, SW8.4, U1.9
unnamed: R7.1, RV1.2
unnamed: SW2.2 (B), U2.13 (~OE), U3.13 (~OE)
unnamed: U2.9 (QH'), U3.14 (SER)
PRD: ROM1.22 (~OE), SW3.2 (B)
PWR: ROM1.27 (~WE), SW11.2 (B)

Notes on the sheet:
Arduino EEPROM Programmer
Chip Select
System Memory
Adjustable Clock
Oscillator Clock
System ROM
CPU Clock
CPU
8KB offset: 8KB
System RAM
8KB offset: 0B
Manual Debounced Clock

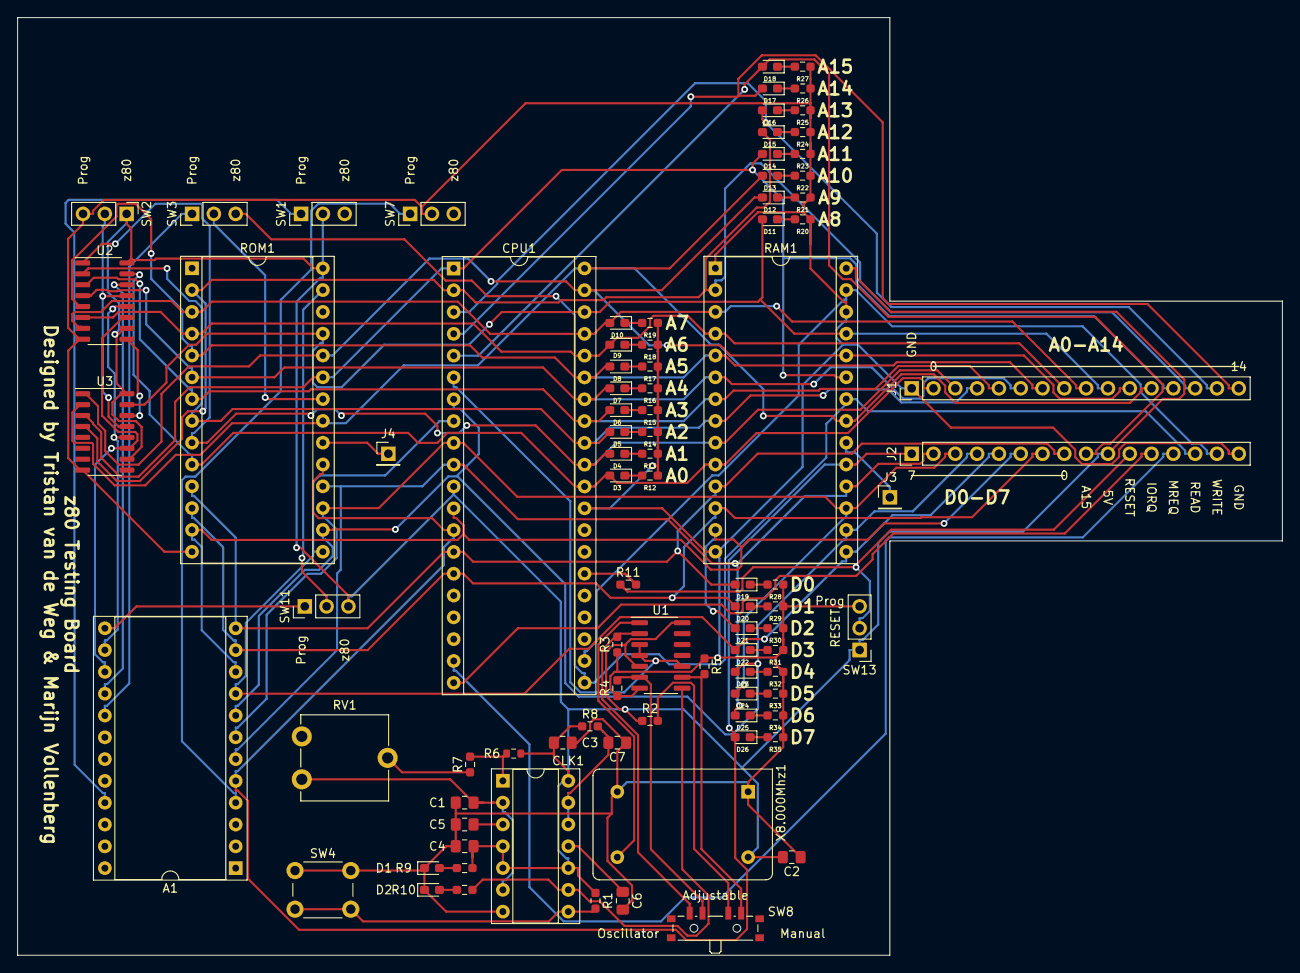
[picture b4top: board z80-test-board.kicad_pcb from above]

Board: 2 copper layers, 147.3 x 109.2 mm, 90 parts (0 on the bottom side), 85 nets.

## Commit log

2021-10-26 * Added Arduino Programmer code, Schematic changes
2021-11-04 Update issue templates
2021-11-04 first assembly test and assembler added
2021-11-04 Set theme jekyll-theme-cayman
2021-11-15 Create index.html
    Wow
2021-11-26 Added picture
2021-11-28 Added python programmer interface
2021-11-28 added python programmer screenshots
2021-12-01 schematic changes
2022-02-11 Create LICENSE
2022-04-05 Schematic & eeprom programmer changes
2022-04-27 schematic and pcb changes
2022-11-03 cleaned up files, added script to launch programming tool
2022-11-03 Delete test.asm
    moved to src/asm
2022-11-03 Delete a.out
    moved to src/asm
2022-11-03 Delete test.txt
    moved to src/asm
2022-11-03 Delete z80Computer-v0.1-v1.1.pdf
    moved to z80/plots/schematic
2022-11-03 Delete z80Computer-v0.2.pdf
    moved to z80/plots/schematic
2022-11-03 Delete z80R1.0Clk.pdf
    moved to z80/plots/schematic
2022-11-03 Delete KiCAD directory
    moved to z80/
2023-01-10 Fixed an issue with displaying information
2023-01-10 More fixes
2023-01-11 Changed wxGlade file to fix text being unaccessible
2023-01-11 added gitignore, program changes
2023-01-11 Implemented config parsing & updated .gitignore
2023-01-23 updated gitignore
2023-02-01 aaaaaa
2023-04-17 OS asm, repo cleanup
2023-05-11 Schematic changes, test script
2023-05-14 Schematic cahnges, PCB changes, test asm changes
2023-10-04 progress on programmer interface
2023-10-09 Progress on binary file reading
2023-11-30 Board revision 1
2023-11-30 added custom character sheet and worked on _PrintB
2023-11-30 made changes to characters.inc
2023-12-14 display control changes
2023-12-14 made changes to OS.z80
2024-01-03 Schematic/code changes, updated to 2024
2024-01-03 Move perfboardcard
2024-01-07 Code updates
2024-01-11 Assembly code changes
2024-01-12 Big progress on assembly
2024-01-12 Hello world almost works
2024-01-24 schematic updates, assembly progress
2024-03-15 finished v2 of hardware, updated eeprom prog pins

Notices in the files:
parts and their libraries:
Copyright 2016 Accelerated Designs. All rights reserved.
